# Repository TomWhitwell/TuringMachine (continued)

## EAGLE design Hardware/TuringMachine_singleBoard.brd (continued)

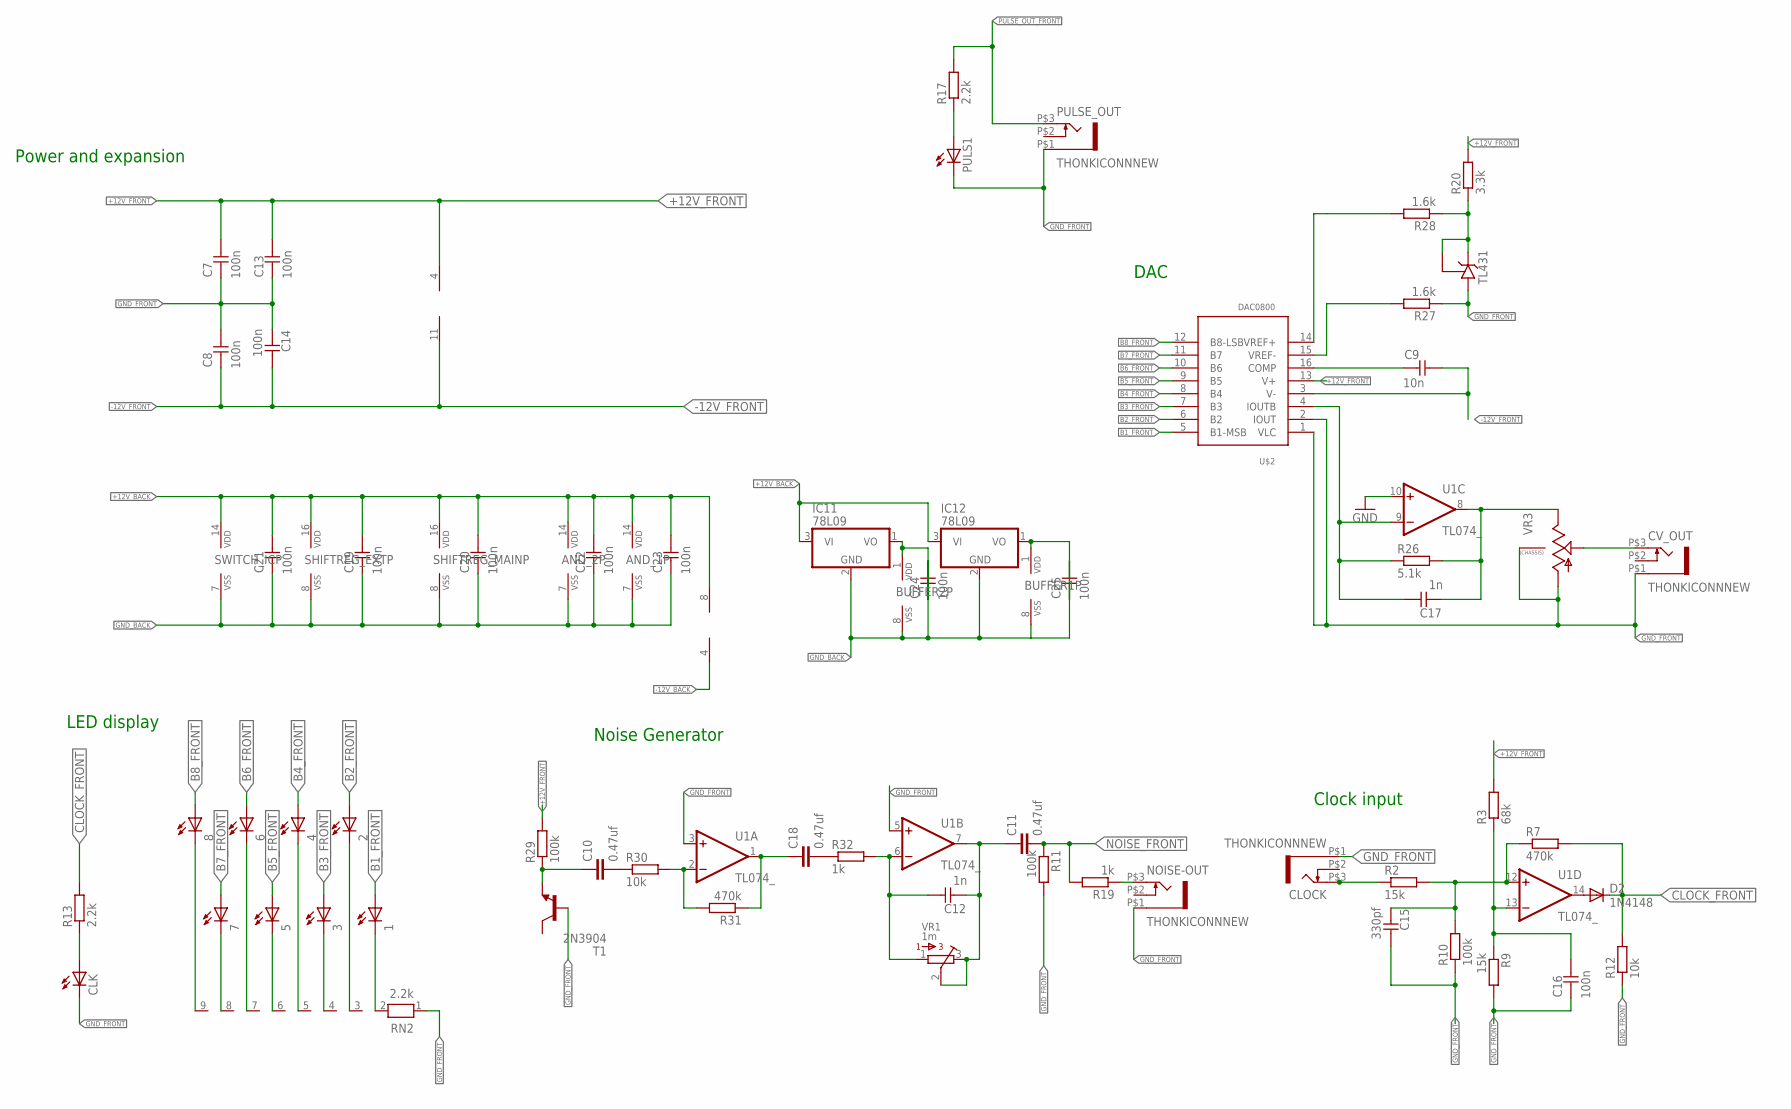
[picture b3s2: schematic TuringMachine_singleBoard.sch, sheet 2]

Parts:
1, 2, 3, 4, 5, 6, 7, 8: LED3MM
AND_1, AND_2: 4081; DIL14
BUFFER1, BUFFER2: 4050; DIL16
C7, C8, C13, C14, C16, C19, C20, C21, C22, C23, C24, C25: 100n; C050-024X044
C9: 10n; C050-024X044
C10, C11, C18: 0.47uf; C050-035X075
C12, C17: 1n; C050-024X044
C15: 330pf; C050-024X044
CLK: LED3MM
CLOCK: THONKICONNNEW; WQP-PJ301M-12_JACK
CV_OUT: THONKICONNNEW; WQP-PJ301M-12_JACK
D2: 1N4148; DO35-7
IC7: TL072P; DIL08
IC11, IC12: 78L09; TO92
NOISE-OUT: THONKICONNNEW; WQP-PJ301M-12_JACK
PULS1: LED3MM
PULSE_OUT: THONKICONNNEW; WQP-PJ301M-12_JACK
R2, R9: 15k; 0207/7
R3: 68k; 0207/7
R7, R31: 470k; 0207/7
R10, R29: 100k; 0207/7
R11: 100k; 7MM_RESISTOR
R12, R30: 10k; 0207/7
R13, R17: 2.2k; 0207/7
R19, R32: 1k; 0207/7
R20: 3.3k; 0207/7
R26: 5.1k; 0207/7
R27, R28: 1.6k; 0207/7
RN2: 2.2k; RN-9
SHIFTREG_EXT: 4015; DIL16
SHIFTREG_MAIN: 4015; DIL16
SWITCH_IC: 4016; DIL14
T1: 2N3904; TO92
TL431: TL431CLP; TO92-CLP
U1: TL074_; DIL14
U$2: DAC0800; DIL16
VR1: 1m; BOURNS_3362P_TRIMMER
VR3: 9MM_SNAP-IN_POT_CHASSIS; 9MM_SNAP-IN_POT

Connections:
+9V_1: BUFFER2.1 (VDD), C24.2, IC11.1 (VO)
+9V_2: BUFFER1.1 (VDD), C25.2, IC12.1 (VO)
+12V_BACK: AND_1.14 (VDD), AND_2.14 (VDD), C19.1, C20.1, C21.1, C22.1, C23.1, IC7.8 (V+), IC11.3 (VI), IC12.3 (VI), SHIFTREG_EXT.16 (VDD), SHIFTREG_MAIN.16 (VDD), SWITCH_IC.14 (VDD); also elsewhere on the board
+12V_FRONT: C7.1, C13.1, R3.2, R20.2, R29.2, U1.4 (V+), U$2.13 (V+); also elsewhere on the board
-12V_BACK: IC7.4 (V-); also elsewhere on the board
-12V_FRONT: C8.2, C9.1, C14.1, U1.11 (V-), U$2.3 (V-); also elsewhere on the board
B1_FRONT: 1.A, U$2.5 (B1-MSB); also elsewhere on the board
B2_FRONT: 2.A, U$2.6 (B2); also elsewhere on the board
B3_FRONT: 3.A, U$2.7 (B3); also elsewhere on the board
B4_FRONT: 4.A, U$2.8 (B4); also elsewhere on the board
B5_FRONT: 5.A, U$2.9 (B5); also elsewhere on the board
B6_FRONT: 6.A, U$2.10 (B6); also elsewhere on the board
B7_FRONT: 7.A, U$2.11 (B7); also elsewhere on the board
B8_FRONT: 8.A, U$2.12 (B8-LSB); also elsewhere on the board
CLOCK_FRONT: D2.C, R7.2, R12.2, R13.2; also elsewhere on the board
GND_BACK: AND_1.7 (VSS), AND_2.7 (VSS), BUFFER1.8 (VSS), BUFFER2.8 (VSS), C19.2, C20.2, C21.2, C22.2, C23.2, C24.1, C25.1, IC11.2 (GND), IC12.2 (GND), SHIFTREG_EXT.8 (VSS), SHIFTREG_MAIN.8 (VSS), SWITCH_IC.7 (VSS); also elsewhere on the board
GND_FRONT: C7.2, C8.1, C13.2, C14.2, C15.1, C16.2, CLK.K (C), CLOCK.P$1 (5), CV_OUT.P$1 (5), NOISE-OUT.P$1 (5), PULS1.K (C), PULSE_OUT.P$1 (5), R9.2, R10.1, R11.2, R12.1, R27.1, RN2.1, T1.2 (B), TL431.A, U1.3 (+IN), U1.5 (+IN), U1.10 (+IN), U$2.1 (VLC), U$2.2 (IOUT), VR3.1 (A), VR3.M1, VR3.M2; also elsewhere on the board
MAIN_OUT: C17.2, R26.2, U1.8 (OUT), VR3.3 (E)
unnamed: CLOCK.P$3 (3), R2.1
unnamed: C15.2, R2.2, R7.1, R10.2, U1.12 (+IN)
unnamed: PULS1.A, R17.1
unnamed: D2.A, U1.14 (OUT)
unnamed: C18.2, R32.1
unnamed: C16.1, R3.1, R9.1, U1.13 (-IN)
unnamed: C17.1, R26.1, U1.9 (-IN), U$2.4 (IOUTB)
unnamed: CLK.A, R13.1
unnamed: C10.1, R29.1, T1.3 (E)
unnamed: R20.1, R28.1, TL431.C, TL431.R
unnamed: C10.2, R30.1
unnamed: R30.2, R31.2, U1.2 (-IN)
unnamed: C18.1, R31.1, U1.1 (OUT)
unnamed: R27.2, U$2.15 (VREF-)
unnamed: C9.2, U$2.16 (COMP)
unnamed: R28.2, U$2.14 (VREF+)
unnamed: C12.1, R32.2, U1.6 (-IN), VR1.1
unnamed: 8.K (C), RN2.9
unnamed: 7.K (C), RN2.8
unnamed: 6.K (C), RN2.7
unnamed: 5.K (C), RN2.6
unnamed: 4.K (C), RN2.5
unnamed: 3.K (C), RN2.4
unnamed: 2.K (C), RN2.3
unnamed: 1.K (C), RN2.2
unnamed: CV_OUT.P$3 (3), VR3.2 (S)
unnamed: NOISE-OUT.P$3 (3), R19.1
unnamed: C11.1, C12.2, U1.7 (OUT), VR1.2, VR1.3
NOISE_FRONT: C11.2, R11.1, R19.2; also elsewhere on the board
PULSE_OUT_FRONT: PULSE_OUT.P$3 (3), R17.2; also elsewhere on the board

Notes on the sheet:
LED display
Noise Generator
Clock input
Power and expansion
DAC

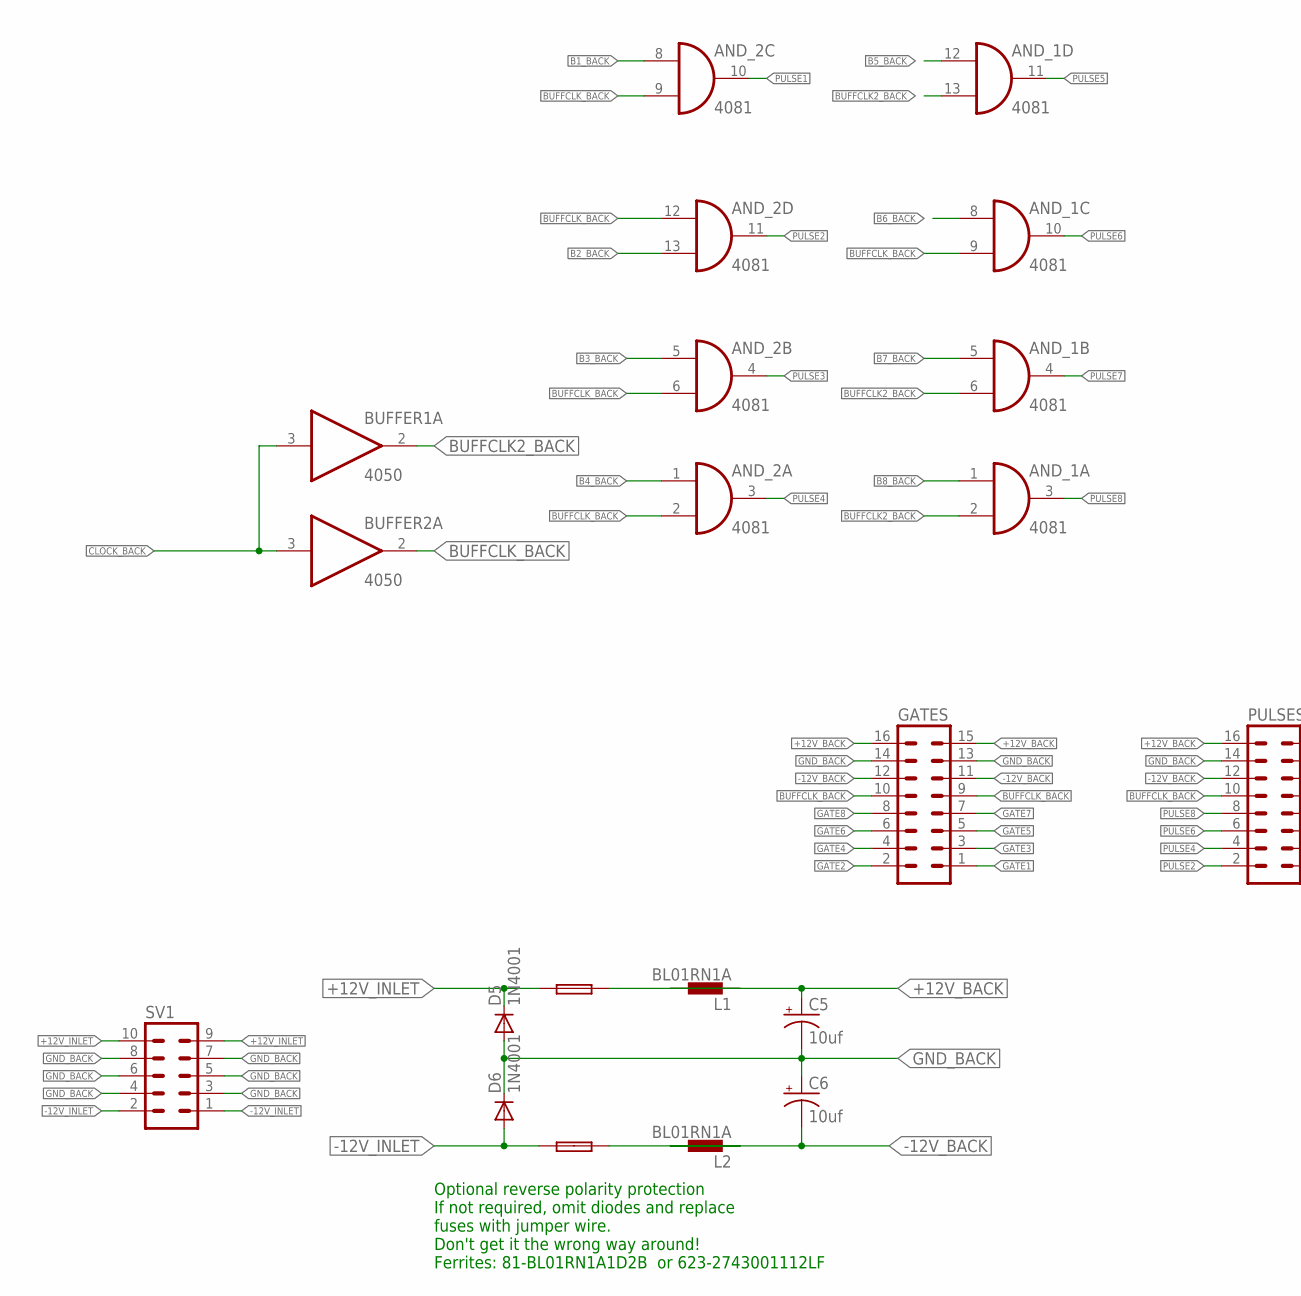
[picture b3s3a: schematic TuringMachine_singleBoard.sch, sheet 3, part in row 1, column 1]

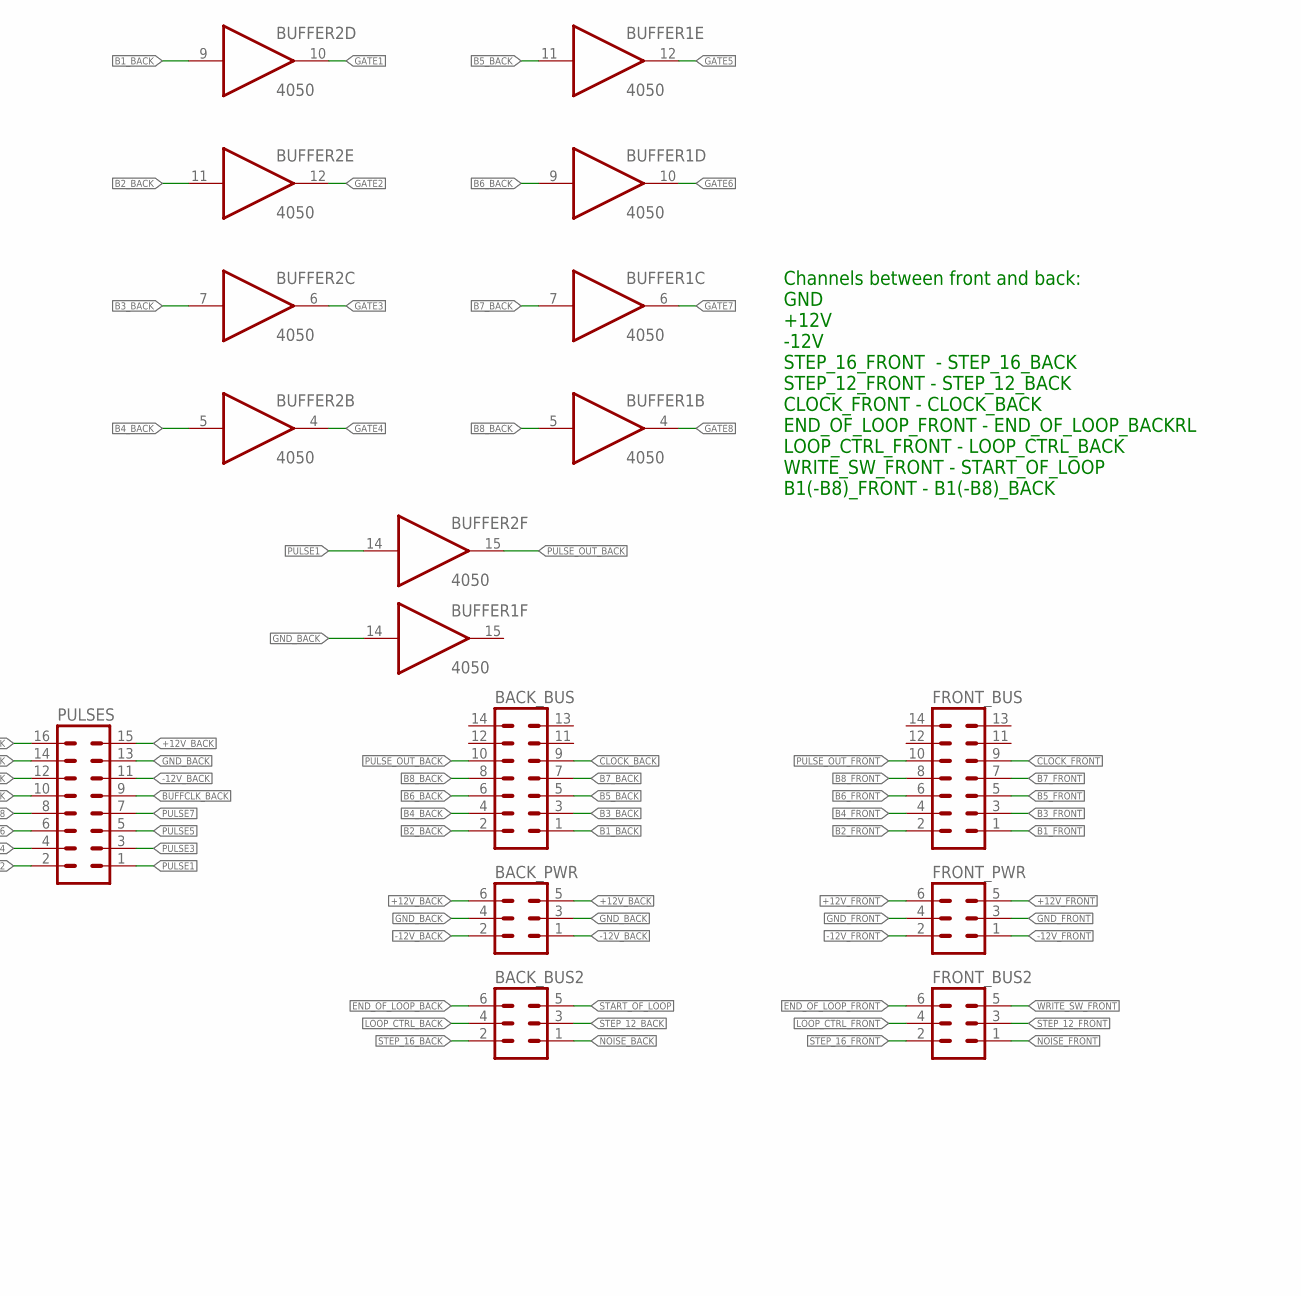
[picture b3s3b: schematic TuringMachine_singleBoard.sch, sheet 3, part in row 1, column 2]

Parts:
AND_1, AND_2: 4081; DIL14
BACK_BUS: MA07-2_BACKSIDEFRONTSIDE; MA07-2
BACK_BUS2: MA03-2
BACK_PWR: MA03-2
BUFFER1, BUFFER2: 4050; DIL16
C5, C6: 10uf; CPOL-RADIAL-10UF-25V
D5, D6: 1N4001; DO41-10
F1, F2: FUSE; C050H075X075
FRONT_BUS: MA07-2_BACKSIDEBACKSIDE; MA07-2_BACKSIDE
FRONT_BUS2: MA03-2BACKSIDE
FRONT_PWR: MA03-2BACKSIDE
GATES: MA08-2
L1, L2: BL01RN1A
PULSES: MA08-2
SV1: 10_PIN_HEADER; MA05-2

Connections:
+12V_BACK: BACK_PWR.5, BACK_PWR.6, C5.1 (+), GATES.15, GATES.16, L1.2, PULSES.15, PULSES.16; also elsewhere on the board
+12V_FRONT: FRONT_PWR.5, FRONT_PWR.6; also elsewhere on the board
+12V_INLET: D5.C, F1.1, SV1.9, SV1.10
-12V_BACK: BACK_PWR.1, BACK_PWR.2, C6.2 (-), GATES.11, GATES.12, L2.2, PULSES.11, PULSES.12; also elsewhere on the board
-12V_FRONT: FRONT_PWR.1, FRONT_PWR.2; also elsewhere on the board
-12V_INLET: D6.A, F2.1, SV1.1, SV1.2
B1_BACK: AND_2.8 (I0), BACK_BUS.1, BUFFER2.9 (I); also elsewhere on the board
B1_FRONT: FRONT_BUS.1; also elsewhere on the board
B2_BACK: AND_2.13 (I1), BACK_BUS.2, BUFFER2.11 (I); also elsewhere on the board
B2_FRONT: FRONT_BUS.2; also elsewhere on the board
B3_BACK: AND_2.5 (I0), BACK_BUS.3, BUFFER2.7 (I); also elsewhere on the board
B3_FRONT: FRONT_BUS.3; also elsewhere on the board
B4_BACK: AND_2.1 (I0), BACK_BUS.4, BUFFER2.5 (I); also elsewhere on the board
B4_FRONT: FRONT_BUS.4; also elsewhere on the board
B5_BACK: AND_1.12 (I0), BACK_BUS.5, BUFFER1.11 (I); also elsewhere on the board
B5_FRONT: FRONT_BUS.5; also elsewhere on the board
B6_BACK: AND_1.8 (I0), BACK_BUS.6, BUFFER1.9 (I); also elsewhere on the board
B6_FRONT: FRONT_BUS.6; also elsewhere on the board
B7_BACK: AND_1.5 (I0), BACK_BUS.7, BUFFER1.7 (I); also elsewhere on the board
B7_FRONT: FRONT_BUS.7; also elsewhere on the board
B8_BACK: AND_1.1 (I0), BACK_BUS.8, BUFFER1.5 (I); also elsewhere on the board
B8_FRONT: FRONT_BUS.8; also elsewhere on the board
BUFFCLK2_BACK: AND_1.2 (I1), AND_1.6 (I1), AND_1.13 (I1), BUFFER1.2 (O)
BUFFCLK_BACK: AND_1.9 (I1), AND_2.2 (I1), AND_2.6 (I1), AND_2.9 (I1), AND_2.12 (I0), BUFFER2.2 (O), GATES.9, GATES.10, PULSES.9, PULSES.10
CLOCK_BACK: BACK_BUS.9, BUFFER1.3 (I), BUFFER2.3 (I); also elsewhere on the board
CLOCK_FRONT: FRONT_BUS.9; also elsewhere on the board
END_OF_LOOP_BACK: BACK_BUS2.6; also elsewhere on the board
END_OF_LOOP_FRONT: FRONT_BUS2.6; also elsewhere on the board
GATE1: BUFFER2.10 (O), GATES.1
GATE2: BUFFER2.12 (O), GATES.2
GATE3: BUFFER2.6 (O), GATES.3
GATE4: BUFFER2.4 (O), GATES.4
GATE5: BUFFER1.12 (O), GATES.5
GATE6: BUFFER1.10 (O), GATES.6
GATE7: BUFFER1.6 (O), GATES.7
GATE8: BUFFER1.4 (O), GATES.8
GND_BACK: BACK_PWR.3, BACK_PWR.4, BUFFER1.14 (I), C5.2 (-), C6.1 (+), D5.A, D6.C, GATES.13, GATES.14, PULSES.13, PULSES.14, SV1.3, SV1.4, SV1.5, SV1.6, SV1.7, SV1.8; also elsewhere on the board
GND_FRONT: FRONT_PWR.3, FRONT_PWR.4; also elsewhere on the board
LOOP_CTRL_BACK: BACK_BUS2.4; also elsewhere on the board
LOOP_CTRL_FRONT: FRONT_BUS2.4; also elsewhere on the board
unnamed: F1.2, L1.1
unnamed: F2.2, L2.1
NOISE_BACK: BACK_BUS2.1; also elsewhere on the board
NOISE_FRONT: FRONT_BUS2.1; also elsewhere on the board
PULSE1: AND_2.10 (O), BUFFER2.14 (I), PULSES.1
PULSE2: AND_2.11 (O), PULSES.2
PULSE3: AND_2.4 (O), PULSES.3
PULSE4: AND_2.3 (O), PULSES.4
PULSE5: AND_1.11 (O), PULSES.5
PULSE6: AND_1.10 (O), PULSES.6
PULSE7: AND_1.4 (O), PULSES.7
PULSE8: AND_1.3 (O), PULSES.8
PULSE_OUT_BACK: BACK_BUS.10, BUFFER2.15 (O)
PULSE_OUT_FRONT: FRONT_BUS.10; also elsewhere on the board
START_OF_LOOP: BACK_BUS2.5; also elsewhere on the board
STEP_12_BACK: BACK_BUS2.3; also elsewhere on the board
STEP_12_FRONT: FRONT_BUS2.3; also elsewhere on the board
STEP_16_BACK: BACK_BUS2.2; also elsewhere on the board
STEP_16_FRONT: FRONT_BUS2.2; also elsewhere on the board
WRITE_SW_FRONT: FRONT_BUS2.5; also elsewhere on the board

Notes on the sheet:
Optional reverse polarity protection If not required, omit diodes and replace fuses with jumper wire. Don't get it the wrong way around! Ferrites: 81-BL01RN1A1D2B or 623-2743001112LF
Channels between front and back: GND +12V -12V STEP_16_FRONT - STEP_16_BACK STEP_12_FRONT - STEP_12_BACK CLOCK_FRONT - CLOCK_BACK END_OF_LOOP_FRONT - END_OF_LOOP_BACKRL LOOP_CTRL_FRONT - LOOP_CTRL_BACK WRITE_SW_FRONT - START_OF_LOOP B1(-B8)_FRONT - B1(-B8)_BACK

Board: 4 copper layers, 111 parts (3 on the bottom side), 104 nets, no tracks yet.

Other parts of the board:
U$1, U$3, U$4, U$5: MOUNTING_HOLE

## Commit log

2015-03-14 Upload rev4 build
2015-03-14 Laid out & routed board with rotary switch
    Need to print and check
2015-03-15 tweaks
2015-03-16 Hand routing
2015-03-16 manual routing
2015-03-17 routing
2015-03-18 Prototype 1 complete and sent to OSHPark
2015-04-11 Added BOM
2015-07-22 Update R32 in noise and R6 in CV input
2015-07-25 Move R16 & C4 to start of loop
2015-07-25 Remove transistors, replace with 4016 gates
2015-07-25 Fixes #5, fixes #4
2015-07-25 not yet routed
2015-07-25 throwing smd parts on the board
2015-08-19 starting to complete dual pcb schematic
2015-08-20 schematic splitting
2015-08-22 add 100k resistor after noise comparator
2015-08-26 Adding pulse out
2015-08-26 Before board split
2015-08-28 Back board routed!
2015-08-29 Starting to route front board
2015-09-06 Layouts
2015-09-13 routing tweaks on back panel
2015-09-13 Front board routed awaiting checking and optimisation
2015-09-13 tidy up schematics
2015-09-14 Create Panel
    Placed holes - need to move and create board size pcb
2015-09-17 fix sizing and add mounting holes
2015-09-18 Completed panel
    Gold on matte
2015-09-24 clean up front layout
2015-09-25 cosmetic routing changes
2015-09-27 Routing tweaks
2015-09-27 StillTweaking
2015-09-27 Finalised Designs + Gerbers
    First prototype for two-board design with PCB panel and built in
    Backpack
2015-10-23 pot values
2015-11-01 Add rotary switch pic
2016-01-03 Cosmetic changes to IC appearance
    Fixes #17, Fixes #13
2016-01-03 minor rerouting
    Fixes #22, fixes #21
2016-01-03 Rev 4 Front and Back Boards complete
2016-01-03 Trimmer hole Fixes #19
2016-01-04 Panel tweaks
2016-01-12 Finalised V4 PCBs
2016-01-22 Silkscreen change on Back Board
    Added + - symbols to fuses in power supply
2016-01-27 Update front board to fix error in ground plane
2016-02-23 Front board updated with new Write switch component
    Slightly enlarged holes to accommodate 2.03 x 0.76 solder tags
2016-02-29 Front board silkscreen change: tidy up new switch markings
2016-03-19 Schematic fixed, back board needs to be routed
2016-03-19 routing started
2016-03-20 First fully routed
2016-03-20 Finished routing + gerber uploaded
2016-04-06 image
2016-04-06 Folder changes
2016-04-06 Upload Panel Artwork
2016-04-07 draft moms
2016-05-28 Upload Schematic PDF
    Closes #27
2017-02-19 removing old BOM
2017-08-07 Increased spacing around ground planes
2017-12-22 upload rev5 ground plane fix gerbers
2018-01-15 Rev 6 Corrects the missing ground connection in Rev 5 Front boards. Rev 6 Front goes with Rev 5 Back.
2019-09-29 Minor fix on line 18, plus added link pdf to Reich's paper
2020-03-22 ignore CAM output in Hardware/ directory
    I generated my own TM Gerbers, for reasons I've long since forgotten,
    and they ended up in the Hardware directory. There's no reason to commit
    them, so don't.
    Thanks for sharing this wonderful project. <3
2021-02-27 Remove trailing spaces on "Panel Artwork" and "PDF_Schematics" folders
2021-03-11 Trimmed spaces from end of path
2021-03-11 Delete Collateral/PDF_Schematics directory
    Duplicate
